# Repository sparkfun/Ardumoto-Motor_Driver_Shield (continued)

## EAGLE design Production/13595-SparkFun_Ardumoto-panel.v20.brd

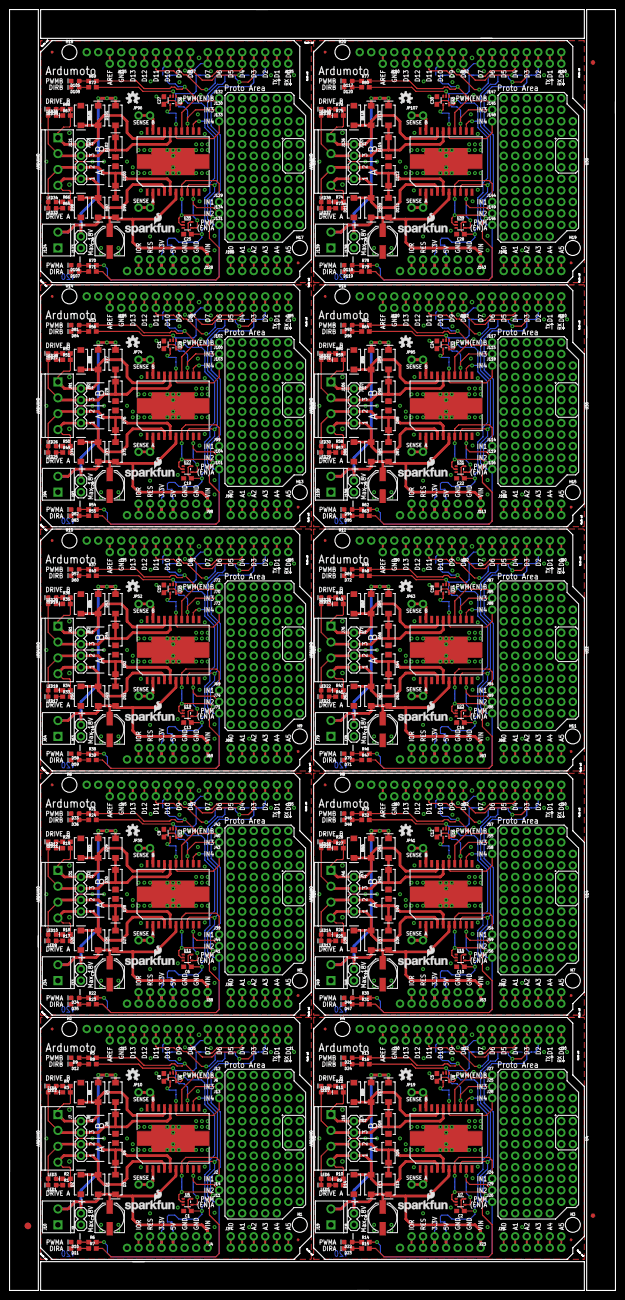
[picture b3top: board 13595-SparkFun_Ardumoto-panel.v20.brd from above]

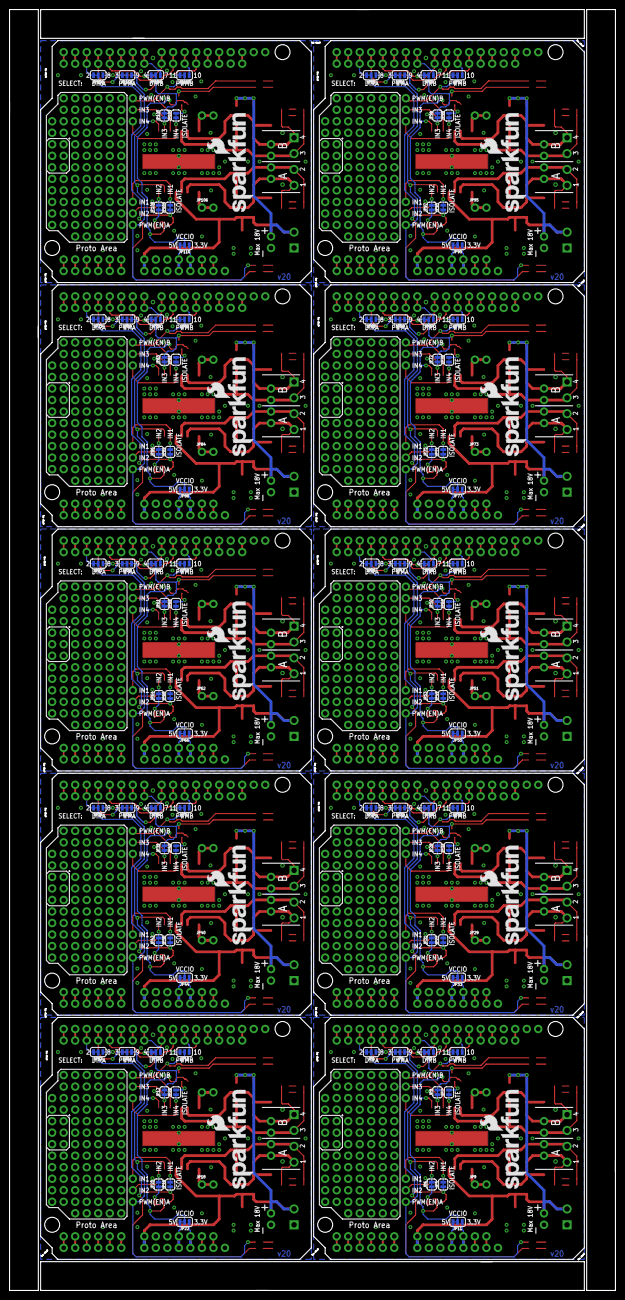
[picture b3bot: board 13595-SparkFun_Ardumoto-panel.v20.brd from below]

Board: 2 copper layers, 133.6 x 282.4 mm, 643 parts (110 on the bottom side), 520 nets.

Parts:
C1, C2, C5, C6, C8, C9, C10, C12, C13, C15, C16, C18, C19, C21, C22, C24, C25, C27, C28, C30: 0.1uF; 0603
C3, C4, C7, C11, C14, C17, C20, C23, C26, C29: 100uF; PANASONIC_D
D1, D2, D3, D4, D5, D6, D7, D8, D13, D14, D15, D16, D17, D18, D19, D20, D25, D26, D27, D28, D29, D30, D31, D32, D37, D38, D39, D40, D41, D42, D43, D44, D49, D50, D51, D52, D53, D54, D55, D56, D61, D62, D63, D64, D65, D66, D67, D68, D73, D74, D75, D76, D77, D78, D79, D80, D85, D86, D87, D88, D89, D90, D91, D92, D97, D98, D99, D100, D101, D102, D103, D104, D109, D110, D111, D112, D113, D114, D115, D116: 1A/40V/500mV; SMA-DIODE
D9, D10, D11, D12, D21, D22, D23, D24, D33, D34, D35, D36, D45, D46, D47, D48, D57, D58, D59, D60, D69, D70, D71, D72, D81, D82, D83, D84, D93, D94, D95, D96, D105, D106, D107, D108, D117, D118, D119, D120: RED; LED-0603
E$1: FIDUCIAL-1.5X3
E$7, E$8: FIDUCIAL-1X2
FD1, FD2, FD3, FD4, FD5, FD6, FD7, FD8, FD9, FD10, FD11, FD12, FD13, FD14, FD15, FD16, FD17, FD18, FD19, FD20: FIDUCIALUFIDUCIAL; MICRO-FIDUCIAL
H1, H2, H3, H4, H5, H6, H7, H8, H9, H10, H11, H12, H13, H14, H15, H16, H17, H18, H19, H20: STAND-OFF
J1, J20, J35, J50, J65, J80, J95, J110, J125, J140: 1X08_NO_SILK
J2, J6, J11, J12, J13, J14, J24, J25, J26, J27, J28, J29, J39, J40, J41, J42, J43, J44, J54, J55, J56, J57, J58, J59, J69, J70, J71, J72, J73, J74, J84, J85, J86, J87, J88, J89, J99, J100, J101, J102, J103, J104, J114, J115, J116, J117, J118, J119, J129, J130, J131, J132, J133, J134, J144, J145, J146, J147, J148, J149: 1X01_NO_SILK
J3, J5, J21, J22, J36, J37, J51, J52, J66, J67, J81, J82, J96, J97, J111, J112, J126, J127, J141, J142: 1X06_NO_SILK
J4, J23, J38, J53, J68, J83, J98, J113, J128, J143: 1X07_NO_SILK
J7, J16, J31, J46, J61, J76, J91, J106, J121, J136: SCREWTERMINAL-3.5MM-4
J8, J17, J32, J47, J62, J77, J92, J107, J122, J137: 1X04
J9, J18, J33, J48, J63, J78, J93, J108, J123, J138: 1X02
J10, J19, J34, J49, J64, J79, J94, J109, J124, J139: SCREWTERMINAL-3.5MM-2
J15, J30, J45, J60, J75, J90, J105, J120, J135, J150: 1X02_NO_SILK
JP1, JP2, JP3, JP4, JP11, JP12, JP13, JP14, JP15, JP22, JP23, JP24, JP25, JP26, JP33, JP34, JP35, JP36, JP37, JP44, JP45, JP46, JP47, JP48, JP55, JP56, JP57, JP58, JP59, JP66, JP67, JP68, JP69, JP70, JP77, JP78, JP79, JP80, JP81, JP88, JP89, JP90, JP91, JP92, JP99, JP100, JP101, JP102, JP103, JP110: 31NCT; SMT-JUMPER_3_1-NC_TRACE_SILK
JP5, JP6, JP7, JP8, JP16, JP17, JP20, JP21, JP27, JP28, JP31, JP32, JP38, JP39, JP42, JP43, JP49, JP50, JP53, JP54, JP60, JP61, JP64, JP65, JP71, JP72, JP75, JP76, JP82, JP83, JP86, JP87, JP93, JP94, JP97, JP98, JP104, JP105, JP108, JP109: 2NCT; SMT-JUMPER_2_NC_TRACE_SILK
JP9, JP10, JP18, JP19, JP29, JP30, JP40, JP41, JP51, JP52, JP62, JP63, JP73, JP74, JP84, JP85, JP95, JP96, JP106, JP107: 1X02_NO_SILK
LED1, LED2, LED5, LED7, LED9, LED11, LED13, LED15, LED17, LED19, LED21, LED23, LED25, LED27, LED29, LED31, LED33, LED35, LED37, LED39: Yellow; LED-0603
LED3, LED4, LED6, LED8, LED10, LED12, LED14, LED16, LED18, LED20, LED22, LED24, LED26, LED28, LED30, LED32, LED34, LED36, LED38, LED40: BLUE; LED-0603
LOGO1, LOGO3, LOGO5, LOGO7, LOGO9, LOGO11, LOGO13, LOGO15, LOGO17, LOGO19: SFE_LOGO_NAME_FLAME.2_INCH; SFE_LOGO_NAME_FLAME_.2
LOGO2, LOGO4, LOGO6, LOGO8, LOGO10, LOGO12, LOGO14, LOGO16, LOGO18, LOGO20: SFE_LOGO_NAME_FLAME.1_INCH; SFE_LOGO_NAME_FLAME_.1
R1, R2, R3, R4, R5, R6, R7, R8, R9, R10, R11, R12, R13, R14, R15, R16, R17, R18, R19, R20, R21, R22, R23, R24, R25, R26, R27, R28, R29, R30, R31, R32, R33, R34, R35, R36, R37, R38, R39, R40, R41, R42, R43, R44, R45, R46, R47, R48, R49, R50, R51, R52, R53, R54, R55, R56, R57, R58, R59, R60, R61, R62, R63, R64, R65, R66, R67, R68, R69, R70, R71, R72, R73, R74, R75, R76, R77, R78, R79, R80: 1k; 0603
U1, U4, U10, U14, U18, U22, U26, U30, U34, U38: ARDUINO; UNO_R3_SHIELD_NOLABELS
U2, U3, U9, U13, U17, U21, U25, U29, U33, U37: L298; POWERSO20_L298_PAD
U5, U6, U7, U8, U11, U12, U15, U16, U19, U20, U23, U24, U27, U28, U31, U32, U35, U36, U39, U40: 74HC1G04; SOT353
U$1, U$2, U$3, U$4, U$5, U$6, U$7, U$8, U$9, U$10: OSHW-LOGOS; OSHW-LOGO-S

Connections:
3.3V: J4.5, JP11.1, U1.3.3V
3.3V1: J23.5, JP22.1, U4.3.3V
3.3V2: J38.5, JP33.1, U10.3.3V
3.3V3: J53.5, JP44.1, U14.3.3V
3.3V4: J68.5, JP55.1, U18.3.3V
3.3V5: J83.5, JP66.1, U22.3.3V
3.3V6: J98.5, JP77.1, U26.3.3V
3.3V7: J113.5, JP88.1, U30.3.3V
3.3V8: J128.5, JP99.1, U34.3.3V
3.3V9: J143.5, JP110.1, U38.3.3V
5V: J4.4, JP11.3, U1.5V
5V1: J23.4, JP22.3, U4.5V
5V2: J38.4, JP33.3, U10.5V
5V3: J53.4, JP44.3, U14.5V
5V4: J68.4, JP55.3, U18.5V
5V5: J83.4, JP66.3, U22.5V
5V6: J98.4, JP77.3, U26.5V
5V7: J113.4, JP88.3, U30.5V
5V8: J128.4, JP99.3, U34.5V
5V9: J143.4, JP110.3, U38.5V
D0: J1.1, U1.RX
D1: J1.2, U1.TX
D2: J1.3, JP1.3, U1.D2
D3: J1.4, JP2.3, U1.D3
D4: J1.5, JP3.3, U1.D4
D5: J1.6, U1.D5
D6: J1.7, U1.D6
D7: J1.8, JP3.1, U1.D7
D8: J5.1, JP1.1, U1.D8
D9: J5.2, JP2.1, U1.D9
D10: J5.3, JP4.1, U1.D10
D11: J5.4, JP4.3, U1.D11
D12: J5.5, U1.D12
D13: J5.6, U1.D13
D14: J22.1, JP13.1, U4.D8
D15: J20.8, JP12.1, U4.D7
D16: J20.1, U4.RX
D17: J20.2, U4.TX
D18: J20.3, JP13.3, U4.D2
D19: J20.5, JP12.3, U4.D4
D20: J20.7, U4.D6
D21: J20.6, U4.D5
D22: J22.3, JP15.1, U4.D10
D23: J22.2, JP14.1, U4.D9
D24: J20.4, JP14.3, U4.D3
D25: J22.4, JP15.3, U4.D11
D26: J22.5, U4.D12
D27: J22.6, U4.D13
D28: J37.1, JP24.1, U10.D8
D29: J35.8, JP23.1, U10.D7
D30: J35.1, U10.RX
D31: J35.2, U10.TX
D32: J35.3, JP24.3, U10.D2
D33: J35.5, JP23.3, U10.D4
D34: J35.7, U10.D6
D35: J35.6, U10.D5
D36: J37.3, JP26.1, U10.D10
D37: J37.2, JP25.1, U10.D9
D38: J35.4, JP25.3, U10.D3
D39: J37.4, JP26.3, U10.D11
D40: J37.5, U10.D12
D41: J37.6, U10.D13
D42: J52.1, JP35.1, U14.D8
D43: J50.8, JP34.1, U14.D7
D44: J50.1, U14.RX
D45: J50.2, U14.TX
D46: J50.3, JP35.3, U14.D2
D47: J50.5, JP34.3, U14.D4
D48: J50.7, U14.D6
D49: J50.6, U14.D5
D50: J52.3, JP37.1, U14.D10
D51: J52.2, JP36.1, U14.D9
D52: J50.4, JP36.3, U14.D3
D53: J52.4, JP37.3, U14.D11
D54: J52.5, U14.D12
D55: J52.6, U14.D13
D56: J67.1, JP46.1, U18.D8
D57: J65.8, JP45.1, U18.D7
D58: J65.1, U18.RX
D59: J65.2, U18.TX
D60: J65.3, JP46.3, U18.D2
D61: J65.5, JP45.3, U18.D4
D62: J65.7, U18.D6
D63: J65.6, U18.D5
D64: J67.3, JP48.1, U18.D10
D65: J67.2, JP47.1, U18.D9
D66: J65.4, JP47.3, U18.D3
D67: J67.4, JP48.3, U18.D11
D68: J67.5, U18.D12
D69: J67.6, U18.D13
D70: J82.1, JP57.1, U22.D8
D71: J80.8, JP56.1, U22.D7
D72: J80.1, U22.RX
D73: J80.2, U22.TX
D74: J80.3, JP57.3, U22.D2
D75: J80.5, JP56.3, U22.D4
D76: J80.7, U22.D6
D77: J80.6, U22.D5
D78: J82.3, JP59.1, U22.D10
D79: J82.2, JP58.1, U22.D9
D80: J80.4, JP58.3, U22.D3
D81: J82.4, JP59.3, U22.D11
D82: J82.5, U22.D12
D83: J82.6, U22.D13
D84: J97.1, JP68.1, U26.D8
D85: J95.8, JP67.1, U26.D7
D86: J95.1, U26.RX
D87: J95.2, U26.TX
D88: J95.3, JP68.3, U26.D2
D89: J95.5, JP67.3, U26.D4
D90: J95.7, U26.D6
D91: J95.6, U26.D5
D92: J97.3, JP70.1, U26.D10
D93: J97.2, JP69.1, U26.D9
D94: J95.4, JP69.3, U26.D3
D95: J97.4, JP70.3, U26.D11
D96: J97.5, U26.D12
D97: J97.6, U26.D13
D98: J112.1, JP79.1, U30.D8
D99: J110.8, JP78.1, U30.D7
D100: J110.1, U30.RX
D101: J110.2, U30.TX
D102: J110.3, JP79.3, U30.D2
D103: J110.5, JP78.3, U30.D4
D104: J110.7, U30.D6
D105: J110.6, U30.D5
D106: J112.3, JP81.1, U30.D10
D107: J112.2, JP80.1, U30.D9
D108: J110.4, JP80.3, U30.D3
D109: J112.4, JP81.3, U30.D11
D110: J112.5, U30.D12
D111: J112.6, U30.D13
D112: J127.1, JP90.1, U34.D8
D113: J125.8, JP89.1, U34.D7
D114: J125.1, U34.RX
D115: J125.2, U34.TX
D116: J125.3, JP90.3, U34.D2
D117: J125.5, JP89.3, U34.D4
D118: J125.7, U34.D6
D119: J125.6, U34.D5
D120: J127.3, JP92.1, U34.D10
D121: J127.2, JP91.1, U34.D9
D122: J125.4, JP91.3, U34.D3
D123: J127.4, JP92.3, U34.D11
D124: J127.5, U34.D12
D125: J127.6, U34.D13
D126: J142.1, JP101.1, U38.D8
D127: J140.8, JP100.1, U38.D7
D128: J140.1, U38.RX
D129: J140.2, U38.TX
D130: J140.3, JP101.3, U38.D2
D131: J140.5, JP100.3, U38.D4
D132: J140.7, U38.D6
D133: J140.6, U38.D5
D134: J142.3, JP103.1, U38.D10
D135: J142.2, JP102.1, U38.D9
D136: J140.4, JP102.3, U38.D3
D137: J142.4, JP103.3, U38.D11
D138: J142.5, U38.D12
D139: J142.6, U38.D13
DIRA: JP1.2, JP5.1, R7.2, U5.2
DIRA1: JP13.2, JP16.1, R15.2, U7.2
DIRA2: JP24.2, JP27.1, R23.2, U11.2
DIRA3: JP35.2, JP38.1, R31.2, U15.2
DIRA4: JP46.2, JP49.1, R39.2, U19.2
DIRA5: JP57.2, JP60.1, R47.2, U23.2
DIRA6: JP68.2, JP71.1, R55.2, U27.2
DIRA7: JP79.2, JP82.1, R63.2, U31.2
DIRA8: JP90.2, JP93.1, R71.2, U35.2
DIRA9: JP101.2, JP104.1, R79.2, U39.2
DIRB: JP3.2, JP8.2, R8.2, U6.2
DIRB1: JP12.2, JP17.2, R16.2, U8.2
DIRB2: JP23.2, JP28.2, R24.2, U12.2
DIRB3: JP34.2, JP39.2, R32.2, U16.2
DIRB4: JP45.2, JP50.2, R40.2, U20.2
DIRB5: JP56.2, JP61.2, R48.2, U24.2
DIRB6: JP67.2, JP72.2, R56.2, U28.2
DIRB7: JP78.2, JP83.2, R64.2, U32.2
DIRB8: JP89.2, JP94.2, R72.2, U36.2
DIRB9: JP100.2, JP105.2, R80.2, U40.2
GND: C1.2, C3.-, C8.2, D2.A, D4.A, D6.A, D8.A, D9.C, D10.C, D11.C, D12.C, J4.2, J4.3, J9.1, J10.1, J15.1, JP9.2, JP10.1, U1.GND@0, U1.GND@1, U1.GND@2, U2.1, U2.10, U2.11, U2.20, U2.PAD, U5.3, U6.3
GND1: C2.2, C4.-, C5.2, D14.A, D16.A, D18.A, D20.A, D21.C, D22.C, D23.C, D24.C, J18.1, J19.1, J23.2, J23.3, J30.1, JP18.2, JP19.1, U3.1, U3.10, U3.11, U3.20, U3.PAD, U4.GND@0, U4.GND@1, U4.GND@2, U7.3, U8.3
GND2: C6.2, C7.-, C9.2, D26.A, D28.A, D30.A, D32.A, D33.C, D34.C, D35.C, D36.C, J33.1, J34.1, J38.2, J38.3, J45.1, JP29.2, JP30.1, U9.1, U9.10, U9.11, U9.20, U9.PAD, U10.GND@0, U10.GND@1, U10.GND@2, U11.3, U12.3
GND3: C10.2, C11.-, C12.2, D38.A, D40.A, D42.A, D44.A, D45.C, D46.C, D47.C, D48.C, J48.1, J49.1, J53.2, J53.3, J60.1, JP40.2, JP41.1, U13.1, U13.10, U13.11, U13.20, U13.PAD, U14.GND@0, U14.GND@1, U14.GND@2, U15.3, U16.3
GND4: C13.2, C14.-, C15.2, D50.A, D52.A, D54.A, D56.A, D57.C, D58.C, D59.C, D60.C, J63.1, J64.1, J68.2, J68.3, J75.1, JP51.2, JP52.1, U17.1, U17.10, U17.11, U17.20, U17.PAD, U18.GND@0, U18.GND@1, U18.GND@2, U19.3, U20.3
GND5: C16.2, C17.-, C18.2, D62.A, D64.A, D66.A, D68.A, D69.C, D70.C, D71.C, D72.C, J78.1, J79.1, J83.2, J83.3, J90.1, JP62.2, JP63.1, U21.1, U21.10, U21.11, U21.20, U21.PAD, U22.GND@0, U22.GND@1, U22.GND@2, U23.3, U24.3
GND6: C19.2, C20.-, C21.2, D74.A, D76.A, D78.A, D80.A, D81.C, D82.C, D83.C, D84.C, J93.1, J94.1, J98.2, J98.3, J105.1, JP73.2, JP74.1, U25.1, U25.10, U25.11, U25.20, U25.PAD, U26.GND@0, U26.GND@1, U26.GND@2, U27.3, U28.3
GND7: C22.2, C23.-, C24.2, D86.A, D88.A, D90.A, D92.A, D93.C, D94.C, D95.C, D96.C, J108.1, J109.1, J113.2, J113.3, J120.1, JP84.2, JP85.1, U29.1, U29.10, U29.11, U29.20, U29.PAD, U30.GND@0, U30.GND@1, U30.GND@2, U31.3, U32.3
GND8: C25.2, C26.-, C27.2, D98.A, D100.A, D102.A, D104.A, D105.C, D106.C, D107.C, D108.C, J123.1, J124.1, J128.2, J128.3, J135.1, JP95.2, JP96.1, U33.1, U33.10, U33.11, U33.20, U33.PAD, U34.GND@0, U34.GND@1, U34.GND@2, U35.3, U36.3
GND9: C28.2, C29.-, C30.2, D110.A, D112.A, D114.A, D116.A, D117.C, D118.C, D119.C, D120.C, J138.1, J139.1, J143.2, J143.3, J150.1, JP106.2, JP107.1, U37.1, U37.10, U37.11, U37.20, U37.PAD, U38.GND@0, U38.GND@1, U38.GND@2, U39.3, U40.3
IN1: J2.1, JP5.2, U2.7
IN2: J14.1, JP6.2, U2.9
IN3: J6.1, JP8.1, U2.13
IN4: J13.1, JP7.1, U2.15
IN5: J29.1, JP20.2, U3.9
IN6: J28.1, JP21.1, U3.15
IN7: J24.1, JP16.2, U3.7
IN8: J25.1, JP17.1, U3.13
IN9: J44.1, JP31.2, U9.9
IN10: J43.1, JP32.1, U9.15
IN11: J39.1, JP27.2, U9.7
IN12: J40.1, JP28.1, U9.13
IN13: J59.1, JP42.2, U13.9
IN14: J58.1, JP43.1, U13.15
IN15: J54.1, JP38.2, U13.7
IN16: J55.1, JP39.1, U13.13
IN17: J74.1, JP53.2, U17.9
IN18: J73.1, JP54.1, U17.15
IN19: J69.1, JP49.2, U17.7
IN20: J70.1, JP50.1, U17.13
IN21: J89.1, JP64.2, U21.9
IN22: J88.1, JP65.1, U21.15
IN23: J84.1, JP60.2, U21.7
IN24: J85.1, JP61.1, U21.13
IN25: J104.1, JP75.2, U25.9
IN26: J103.1, JP76.1, U25.15
IN27: J99.1, JP71.2, U25.7
IN28: J100.1, JP72.1, U25.13
IN29: J119.1, JP86.2, U29.9
IN30: J118.1, JP87.1, U29.15
IN31: J114.1, JP82.2, U29.7
IN32: J115.1, JP83.1, U29.13
IN33: J134.1, JP97.2, U33.9
IN34: J133.1, JP98.1, U33.15
IN35: J129.1, JP93.2, U33.7
IN36: J130.1, JP94.1, U33.13
IN37: J149.1, JP108.2, U37.9
IN38: J148.1, JP109.1, U37.15
IN39: J144.1, JP104.2, U37.7
IN40: J145.1, JP105.1, U37.13
IOREF: J4.7, U1.IOREF
IOREF1: J23.7, U4.IOREF
IOREF2: J38.7, U10.IOREF
IOREF3: J53.7, U14.IOREF
IOREF4: J68.7, U18.IOREF
IOREF5: J83.7, U22.IOREF
IOREF6: J98.7, U26.IOREF
IOREF7: J113.7, U30.IOREF
IOREF8: J128.7, U34.IOREF
IOREF9: J143.7, U38.IOREF
unnamed: LED1.A, R1.1
unnamed: LED3.C, R2.1
unnamed: LED4.C, R3.1
unnamed: LED2.A, R4.1
unnamed: J15.2, U1.AREF
unnamed: J3.1, U1.A0
unnamed: J3.2, U1.A1
unnamed: J3.3, U1.A2
unnamed: J3.4, U1.A3
unnamed: J3.5, U1.A4
unnamed: J3.6, U1.A5
unnamed: D9.A, R5.1
unnamed: D10.A, R6.1
unnamed: D12.A, R8.1
unnamed: D11.A, R7.1
unnamed: LED5.A, R9.1
unnamed: LED6.C, R10.1
unnamed: LED8.C, R11.1
unnamed: LED7.A, R12.1
unnamed: J21.1, U4.A0
unnamed: J21.2, U4.A1
unnamed: J21.3, U4.A2
unnamed: J21.4, U4.A3
unnamed: J21.5, U4.A4
unnamed: J21.6, U4.A5
unnamed: D21.A, R13.1
unnamed: D22.A, R14.1
unnamed: D24.A, R16.1
unnamed: D23.A, R15.1
unnamed: J30.2, U4.AREF
unnamed: LED9.A, R17.1
unnamed: LED10.C, R18.1
unnamed: LED12.C, R19.1
unnamed: LED11.A, R20.1
unnamed: J36.1, U10.A0
unnamed: J36.2, U10.A1
unnamed: J36.3, U10.A2
unnamed: J36.4, U10.A3
unnamed: J36.5, U10.A4
unnamed: J36.6, U10.A5
unnamed: D33.A, R21.1
unnamed: D34.A, R22.1
unnamed: D36.A, R24.1
unnamed: D35.A, R23.1
unnamed: J45.2, U10.AREF
unnamed: LED13.A, R25.1
unnamed: LED14.C, R26.1
unnamed: LED16.C, R27.1
unnamed: LED15.A, R28.1
unnamed: J51.1, U14.A0
unnamed: J51.2, U14.A1
unnamed: J51.3, U14.A2
unnamed: J51.4, U14.A3
unnamed: J51.5, U14.A4
unnamed: J51.6, U14.A5
unnamed: D45.A, R29.1
unnamed: D46.A, R30.1
unnamed: D48.A, R32.1
unnamed: D47.A, R31.1
unnamed: J60.2, U14.AREF
unnamed: LED17.A, R33.1
unnamed: LED18.C, R34.1
unnamed: LED20.C, R35.1
unnamed: LED19.A, R36.1
unnamed: J66.1, U18.A0
unnamed: J66.2, U18.A1
unnamed: J66.3, U18.A2
unnamed: J66.4, U18.A3
unnamed: J66.5, U18.A4
unnamed: J66.6, U18.A5
unnamed: D57.A, R37.1
unnamed: D58.A, R38.1
unnamed: D60.A, R40.1
unnamed: D59.A, R39.1
unnamed: J75.2, U18.AREF
unnamed: LED21.A, R41.1
unnamed: LED22.C, R42.1
unnamed: LED24.C, R43.1
unnamed: LED23.A, R44.1
unnamed: J81.1, U22.A0
unnamed: J81.2, U22.A1
unnamed: J81.3, U22.A2
unnamed: J81.4, U22.A3
unnamed: J81.5, U22.A4
unnamed: J81.6, U22.A5
unnamed: D69.A, R45.1
unnamed: D70.A, R46.1
unnamed: D72.A, R48.1
unnamed: D71.A, R47.1
unnamed: J90.2, U22.AREF
unnamed: LED25.A, R49.1
unnamed: LED26.C, R50.1
unnamed: LED28.C, R51.1
unnamed: LED27.A, R52.1
unnamed: J96.1, U26.A0
unnamed: J96.2, U26.A1
unnamed: J96.3, U26.A2
unnamed: J96.4, U26.A3
unnamed: J96.5, U26.A4
unnamed: J96.6, U26.A5
unnamed: D81.A, R53.1
unnamed: D82.A, R54.1
unnamed: D84.A, R56.1
unnamed: D83.A, R55.1
unnamed: J105.2, U26.AREF
unnamed: LED29.A, R57.1
unnamed: LED30.C, R58.1
unnamed: LED32.C, R59.1
unnamed: LED31.A, R60.1
unnamed: J111.1, U30.A0
unnamed: J111.2, U30.A1
unnamed: J111.3, U30.A2
unnamed: J111.4, U30.A3
unnamed: J111.5, U30.A4
unnamed: J111.6, U30.A5
unnamed: D93.A, R61.1
unnamed: D94.A, R62.1
unnamed: D96.A, R64.1
unnamed: D95.A, R63.1
unnamed: J120.2, U30.AREF
unnamed: LED33.A, R65.1
unnamed: LED34.C, R66.1
unnamed: LED36.C, R67.1
unnamed: LED35.A, R68.1
unnamed: J126.1, U34.A0
unnamed: J126.2, U34.A1
unnamed: J126.3, U34.A2
unnamed: J126.4, U34.A3
unnamed: J126.5, U34.A4
unnamed: J126.6, U34.A5
unnamed: D105.A, R69.1
unnamed: D106.A, R70.1
unnamed: D108.A, R72.1
unnamed: D107.A, R71.1
unnamed: J135.2, U34.AREF
unnamed: LED37.A, R73.1
unnamed: LED38.C, R74.1
unnamed: LED40.C, R75.1
unnamed: LED39.A, R76.1
unnamed: J141.1, U38.A0
unnamed: J141.2, U38.A1
unnamed: J141.3, U38.A2
unnamed: J141.4, U38.A3
unnamed: J141.5, U38.A4
unnamed: J141.6, U38.A5
unnamed: D117.A, R77.1
unnamed: D118.A, R78.1
unnamed: D120.A, R80.1
unnamed: D119.A, R79.1
unnamed: J150.2, U38.AREF
NDIRA: JP6.1, U5.4
NDIRA1: JP20.1, U7.4
NDIRA2: JP31.1, U11.4
NDIRA3: JP42.1, U15.4
NDIRA4: JP53.1, U19.4
NDIRA5: JP64.1, U23.4
NDIRA6: JP75.1, U27.4
NDIRA7: JP86.1, U31.4
NDIRA8: JP97.1, U35.4
NDIRA9: JP108.1, U39.4
NDIRB: JP7.2, U6.4
NDIRB1: JP21.2, U8.4
NDIRB2: JP32.2, U12.4
NDIRB3: JP43.2, U16.4
NDIRB4: JP54.2, U20.4
NDIRB5: JP65.2, U24.4
NDIRB6: JP76.2, U28.4
NDIRB7: JP87.2, U32.4
NDIRB8: JP98.2, U36.4
NDIRB9: JP109.2, U40.4
OUT1: D1.A, D2.C, J7.4, J8.4, R1.2, R2.2, U2.4
OUT2: D3.A, D4.C, J7.3, J8.3, LED1.C, LED3.A, U2.5
OUT3: D5.A, D6.C, J7.2, J8.2, LED2.C, LED4.A, U2.16
OUT4: D7.A, D8.C, J7.1, J8.1, R3.2, R4.2, U2.17
OUT5: D13.A, D14.C, J16.4, J17.4, R9.2, R10.2, U3.4
OUT6: D15.A, D16.C, J16.3, J17.3, LED5.C, LED6.A, U3.5
OUT7: D19.A, D20.C, J16.1, J17.1, R11.2, R12.2, U3.17
OUT8: D17.A, D18.C, J16.2, J17.2, LED7.C, LED8.A, U3.16
OUT9: D25.A, D26.C, J31.4, J32.4, R17.2, R18.2, U9.4
OUT10: D27.A, D28.C, J31.3, J32.3, LED9.C, LED10.A, U9.5
OUT11: D31.A, D32.C, J31.1, J32.1, R19.2, R20.2, U9.17
OUT12: D29.A, D30.C, J31.2, J32.2, LED11.C, LED12.A, U9.16
OUT13: D37.A, D38.C, J46.4, J47.4, R25.2, R26.2, U13.4
OUT14: D39.A, D40.C, J46.3, J47.3, LED13.C, LED14.A, U13.5
OUT15: D43.A, D44.C, J46.1, J47.1, R27.2, R28.2, U13.17
OUT16: D41.A, D42.C, J46.2, J47.2, LED15.C, LED16.A, U13.16
OUT17: D49.A, D50.C, J61.4, J62.4, R33.2, R34.2, U17.4
OUT18: D51.A, D52.C, J61.3, J62.3, LED17.C, LED18.A, U17.5
OUT19: D55.A, D56.C, J61.1, J62.1, R35.2, R36.2, U17.17
OUT20: D53.A, D54.C, J61.2, J62.2, LED19.C, LED20.A, U17.16
OUT21: D61.A, D62.C, J76.4, J77.4, R41.2, R42.2, U21.4
OUT22: D63.A, D64.C, J76.3, J77.3, LED21.C, LED22.A, U21.5
OUT23: D67.A, D68.C, J76.1, J77.1, R43.2, R44.2, U21.17
OUT24: D65.A, D66.C, J76.2, J77.2, LED23.C, LED24.A, U21.16
OUT25: D73.A, D74.C, J91.4, J92.4, R49.2, R50.2, U25.4
OUT26: D75.A, D76.C, J91.3, J92.3, LED25.C, LED26.A, U25.5
OUT27: D79.A, D80.C, J91.1, J92.1, R51.2, R52.2, U25.17
OUT28: D77.A, D78.C, J91.2, J92.2, LED27.C, LED28.A, U25.16
OUT29: D85.A, D86.C, J106.4, J107.4, R57.2, R58.2, U29.4
OUT30: D87.A, D88.C, J106.3, J107.3, LED29.C, LED30.A, U29.5
OUT31: D91.A, D92.C, J106.1, J107.1, R59.2, R60.2, U29.17
OUT32: D89.A, D90.C, J106.2, J107.2, LED31.C, LED32.A, U29.16
OUT33: D97.A, D98.C, J121.4, J122.4, R65.2, R66.2, U33.4
OUT34: D99.A, D100.C, J121.3, J122.3, LED33.C, LED34.A, U33.5
OUT35: D103.A, D104.C, J121.1, J122.1, R67.2, R68.2, U33.17
OUT36: D101.A, D102.C, J121.2, J122.2, LED35.C, LED36.A, U33.16
OUT37: D109.A, D110.C, J136.4, J137.4, R73.2, R74.2, U37.4
OUT38: D111.A, D112.C, J136.3, J137.3, LED37.C, LED38.A, U37.5
OUT39: D115.A, D116.C, J136.1, J137.1, R75.2, R76.2, U37.17
OUT40: D113.A, D114.C, J136.2, J137.2, LED39.C, LED40.A, U37.16
PWMA: J11.1, JP2.2, R6.2, U2.8
PWMA1: J26.1, JP14.2, R14.2, U3.8
PWMA2: J41.1, JP25.2, R22.2, U9.8
PWMA3: J56.1, JP36.2, R30.2, U13.8
PWMA4: J71.1, JP47.2, R38.2, U17.8
PWMA5: J86.1, JP58.2, R46.2, U21.8
PWMA6: J101.1, JP69.2, R54.2, U25.8
PWMA7: J116.1, JP80.2, R62.2, U29.8
PWMA8: J131.1, JP91.2, R70.2, U33.8
PWMA9: J146.1, JP102.2, R78.2, U37.8
PWMB: J12.1, JP4.2, R5.2, U2.14
PWMB1: J27.1, JP15.2, R13.2, U3.14
PWMB2: J42.1, JP26.2, R21.2, U9.14
PWMB3: J57.1, JP37.2, R29.2, U13.14
PWMB4: J72.1, JP48.2, R37.2, U17.14
PWMB5: J87.1, JP59.2, R45.2, U21.14
PWMB6: J102.1, JP70.2, R53.2, U25.14
PWMB7: J117.1, JP81.2, R61.2, U29.14
PWMB8: J132.1, JP92.2, R69.2, U33.14
PWMB9: J147.1, JP103.2, R77.2, U37.14
RESET: J4.6, U1.RES
RESET1: J23.6, U4.RES
RESET2: J38.6, U10.RES
RESET3: J53.6, U14.RES
RESET4: J68.6, U18.RES
RESET5: J83.6, U22.RES
RESET6: J98.6, U26.RES
RESET7: J113.6, U30.RES
RESET8: J128.6, U34.RES
RESET9: J143.6, U38.RES
SENA: JP9.1, U2.2
SENA1: JP18.1, U3.2
SENA2: JP29.1, U9.2
SENA3: JP40.1, U13.2
SENA4: JP51.1, U17.2
SENA5: JP62.1, U21.2
SENA6: JP73.1, U25.2
SENA7: JP84.1, U29.2
SENA8: JP95.1, U33.2
SENA9: JP106.1, U37.2
SENB: JP10.2, U2.19
SENB1: JP19.2, U3.19
SENB2: JP30.2, U9.19
SENB3: JP41.2, U13.19
SENB4: JP52.2, U17.19
SENB5: JP63.2, U21.19
SENB6: JP74.2, U25.19
SENB7: JP85.2, U29.19
SENB8: JP96.2, U33.19
SENB9: JP107.2, U37.19
VCCIO: C1.1, C8.1, JP11.2, U2.12, U5.5, U6.5
VCCIO1: C2.1, C5.1, JP22.2, U3.12, U7.5, U8.5
VCCIO2: C6.1, C9.1, JP33.2, U9.12, U11.5, U12.5
VCCIO3: C10.1, C12.1, JP44.2, U13.12, U15.5, U16.5
VCCIO4: C13.1, C15.1, JP55.2, U17.12, U19.5, U20.5
VCCIO5: C16.1, C18.1, JP66.2, U21.12, U23.5, U24.5
VCCIO6: C19.1, C21.1, JP77.2, U25.12, U27.5, U28.5
VCCIO7: C22.1, C24.1, JP88.2, U29.12, U31.5, U32.5
VCCIO8: C25.1, C27.1, JP99.2, U33.12, U35.5, U36.5
VCCIO9: C28.1, C30.1, JP110.2, U37.12, U39.5, U40.5
VIN: C3.+, D1.C, D3.C, D5.C, D7.C, J4.1, J9.2, J10.2, U1.VIN, U2.6
VIN1: C4.+, D13.C, D15.C, D17.C, D19.C, J18.2, J19.2, J23.1, U3.6, U4.VIN
VIN2: C7.+, D25.C, D27.C, D29.C, D31.C, J33.2, J34.2, J38.1, U9.6, U10.VIN
VIN3: C11.+, D37.C, D39.C, D41.C, D43.C, J48.2, J49.2, J53.1, U13.6, U14.VIN
VIN4: C14.+, D49.C, D51.C, D53.C, D55.C, J63.2, J64.2, J68.1, U17.6, U18.VIN
VIN5: C17.+, D61.C, D63.C, D65.C, D67.C, J78.2, J79.2, J83.1, U21.6, U22.VIN
VIN6: C20.+, D73.C, D75.C, D77.C, D79.C, J93.2, J94.2, J98.1, U25.6, U26.VIN
VIN7: C23.+, D85.C, D87.C, D89.C, D91.C, J108.2, J109.2, J113.1, U29.6, U30.VIN
VIN8: C26.+, D97.C, D99.C, D101.C, D103.C, J123.2, J124.2, J128.1, U33.6, U34.VIN
VIN9: C29.+, D109.C, D111.C, D113.C, D115.C, J138.2, J139.2, J143.1, U37.6, U38.VIN

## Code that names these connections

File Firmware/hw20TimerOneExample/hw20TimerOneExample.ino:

//This sketch walks through various drive states.
//Use the serial terminal to advance states.  Enter some serial data and press return.
//The sketch only check for the existance of data, not what it is.
//
//The Ardumoto must have all pins set to alternate, timer1 only works on
//pins 9 and 10.
//
//Marshall Taylor
//March 3, 2017

#include "TimerOne.h"

// Clockwise and counter-clockwise definitions.
// Depending on how you wired your motors, you may need to swap.
#define FORWARD  0
#define REVERSE 1

	// Motor definitions to make life easier:
#define MOTOR_A 0
#define MOTOR_B 1

// Pin Assignments //
// Timer1 connects only to PWM pins 9 and 10.

//Alternate pins:
#define DIRA 8 // Direction control for motor A
#define PWMA 9 // PWM control (speed) for motor A
#define DIRB 7 // Direction control for motor B
#define PWMB 10 // PWM control (speed) for motor B

void setup()
{
	Serial.begin(115200);
	setupArdumoto(); // Set all pins as outputs
}

void loop()
{
	int loopRunning = 1;
	int counter = 0;
	int state = 0;
	while( loopRunning == 1 )
	{
		//ramp up
		switch( state )
		{
		case 0:
			driveArdumoto(MOTOR_A, FORWARD, counter);
			driveArdumoto(MOTOR_B, FORWARD, counter);
			counter++;
			if( counter == 256 )
			{
				counter = 255;
				state = 1;
			}
			break;
		case 1:
			driveArdumoto(MOTOR_A, FORWARD, counter);
			driveArdumoto(MOTOR_B, FORWARD, counter);
			counter--;
			if( counter == 1 )
			{
				counter = 0;
				state = 0;
			}
			break;
		case 2:
			break;
		default:
			break;
		}
		delay(3);
		if( Serial.available() )
		{
			loopRunning = 0;
		}
	}
	waitForInput();

	// Now spin both!
	driveArdumoto(MOTOR_A, FORWARD, 255);  // Motor A at max speed.
	driveArdumoto(MOTOR_B, FORWARD, 255);  // Motor B at max speed.
	waitForInput();

	// Now go backwards at half that speed:
	driveArdumoto(MOTOR_A, REVERSE, 127);  // Motor A at max speed.
	driveArdumoto(MOTOR_B, REVERSE, 127);  // Motor B at max speed.
	waitForInput();
	
	stopArdumoto(MOTOR_A);  // STOP motor A 
	stopArdumoto(MOTOR_B);  // STOP motor A 
	waitForInput();
}

// driveArdumoto drives 'motor' in 'dir' direction at 'spd' speed
void driveArdumoto(byte motor, byte dir, byte spd)
{
	if (motor == MOTOR_A)
	{
		digitalWrite(DIRA, dir);
		//analogWrite(PWMA, spd);
		Timer1.pwm(PWMA, spd << 2);
	}
	else if (motor == MOTOR_B)
	{
		digitalWrite(DIRB, dir);
		//analogWrite(PWMB, spd);
		Timer1.pwm(PWMB, spd << 2);
	}  
}

// stopArdumoto makes a motor stop
void stopArdumoto(byte motor)
{
	driveArdumoto(motor, 0, 0);
}

// setupArdumoto initialize all pins
void setupArdumoto()
{
	// All pins should be setup as outputs:
	pinMode(PWMA, OUTPUT);
	pinMode(PWMB, OUTPUT);
	pinMode(DIRA, OUTPUT);
	pinMode(DIRB, OUTPUT);

	// Initialize all pins as low:
	digitalWrite(PWMA, LOW);
	digitalWrite(PWMB, LOW);
	digitalWrite(DIRA, LOW);
	digitalWrite(DIRB, LOW);
 
	Timer1.initialize(200);         // initialize timer1

}

void waitForInput( void )
{
	while( Serial.available() == 0 )
	{
		delay(1);
	}
	while( Serial.available() == 1 )
	{
		Serial.read();
		delay(1);
	}
}

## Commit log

2015-03-12 Adding hardware, firmware
2015-03-12 Adding hardware files for real this time
2016-12-20 Schematic is the same, but all parts have been updated to the new libraries. The layout is no longer valid, and proto area has been moved aside. This is ready for functional changes.
2016-12-21 Schematic changes applied, layout is now mostly ripped up
2016-12-29 Desing ready for proto 1 review
2017-01-06 Touched up the silk a bit in preparation for review
2017-01-09 Going for QC inspection
2017-01-10 Reordered two R3 pins (9 and 6). Switched sheet locations and adjusted logos. Removed invalid airwires
2017-01-10 Moved designer name back into place, checked silk
2017-02-07 Made changes to prototype in preparation for reds
2017-02-07 Added note on VCCIO and nudged traces
2017-02-08 Made post-review changes
2017-02-10 panel
2017-03-16 Added tag links to readme
2017-03-16 switched components LED1 and LED3
2017-03-31 Added example for hookup guide
2017-03-31 added some more examples
2017-04-14 Added picture to readme
2017-04-14 Fixed link
